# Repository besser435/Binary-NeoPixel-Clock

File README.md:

# Lightbeam S3
 
TODO:<br>
Take picutres<br>
Make CP build and upload to CP website<br>

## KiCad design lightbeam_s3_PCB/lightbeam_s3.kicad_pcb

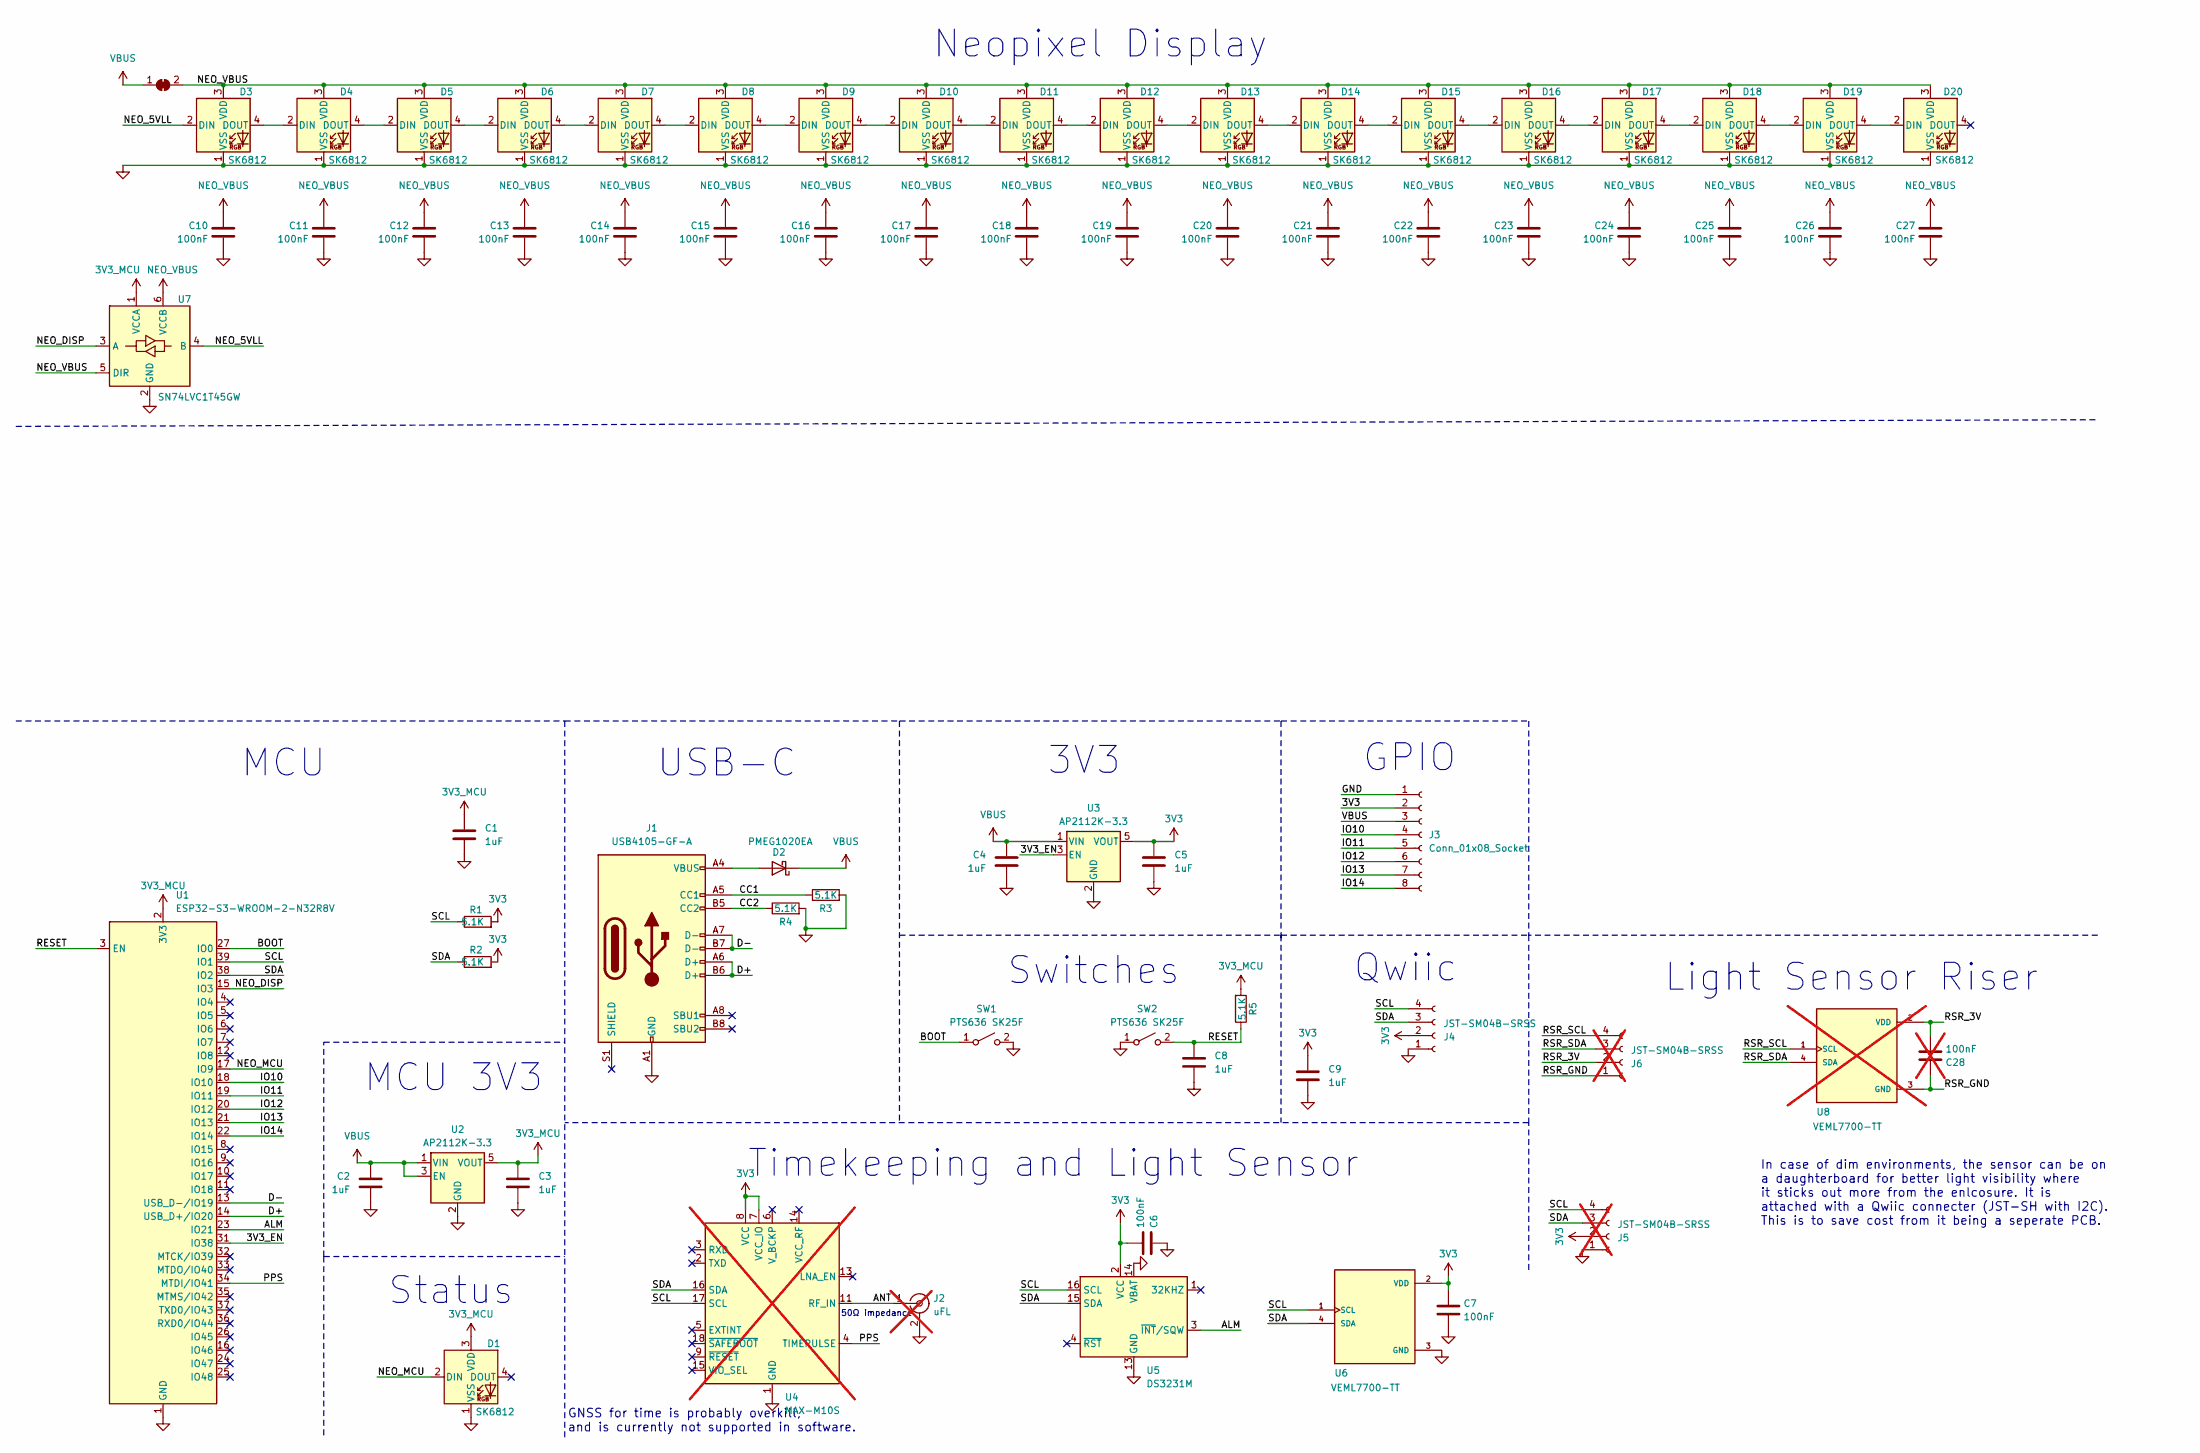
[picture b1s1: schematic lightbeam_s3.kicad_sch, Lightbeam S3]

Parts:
C1, C2, C3, C4, C5, C8, C9: 1uF; C_0603_1608Metric
C6, C7, C10, C11, C12, C13, C14, C15, C16, C17, C18, C19, C20, C21, C22, C23, C24, C25, C26, C27: 100nF; C_0603_1608Metric
C28: 100nF; C_0603_1608Metric; not fitted
D1, D3, D4, D5, D6, D7, D8, D9, D10, D11, D12, D13, D14, D15, D16, D17, D18, D19, D20: SK6812; LED_SK6812_PLCC4_5.0x5.0mm_P3.2mm
D2: PMEG1020EA; D_SOD-323
J1: USB4105-GF-A; USB_C_Receptacle_GCT_USB4105-xx-A_16P_TopMnt_Horizontal
J2: uFL; U.FL_Hirose_U.FL-R-SMT-1_Vertical; not fitted
J3: Conn_01x08_Socket; PinHeader_1x08_P2.54mm_Vertical
J4: JST-SM04B-SRSS; JST_SH_SM04B-SRSS-TB_1x04-1MP_P1.00mm_Horizontal
J5, J6: JST-SM04B-SRSS; JST_SH_SM04B-SRSS-TB_1x04-1MP_P1.00mm_Horizontal; not fitted
JP3: SolderJumper_2_Bridged; solder_jumper_bridged
R1, R2, R3, R4, R5: 5.1K; C_0603_1608Metric
SW1, SW2: PTS636 SK25F; SW_Tactile_SPST_NO_Straight_CK_PTS636Sx25SMTRLFS
U1: ESP32-S3-WROOM-2-N32R8V; ESP32-S3-WROOM-2
U2, U3: AP2112K-3.3; SOT-23-5
U4: MAX-M10S; ublox_MAX; not fitted
U5: DS3231M; SOIC-16W_7.5x10.3mm_P1.27mm
U6: VEML7700-TT; VEML7700; PARTREV 1.6
U7: SN74LVC1T45GW; SOT-363_SC-70-6
U8: VEML7700-TT; VEML7700; PARTREV 1.6; not fitted

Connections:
3V3: C5.1, C6.1, C7.2, C9.1, J3.2, J4.2, J5.2, R1.2, R2.2, U3.5 (VOUT), U4.7 (VCC_IO), U4.8 (VCC), U5.2 (VCC), U6.2 (VDD)
3V3_MCU: C1.1, C3.1, D1.3 (VDD), R5.2, U1.2 (3V3), U2.5 (VOUT), U7.1 (VCCA)
/3V3_EN: U1.31 (IO38), U3.3 (EN)
/ALM: U1.23 (IO21), U5.3 (~INT/SQW)
/ANT: J2.1 (In), U4.11 (RF_IN)
/BOOT: SW1.1 (A), U1.27 (IO0)
/CC1: J1.A5 (CC1), R3.1
/CC2: J1.B5 (CC2), R4.1
/D+: J1.A6 (D+), J1.B6 (D+), U1.14 (USB_D+/IO20)
/D-: J1.A7 (D-), J1.B7 (D-), U1.13 (USB_D-/IO19)
/IO10: J3.4, U1.18 (IO10)
/IO11: J3.5, U1.19 (IO11)
/IO12: J3.6, U1.20 (IO12)
/IO13: J3.7, U1.21 (IO13)
/IO14: J3.8, U1.22 (IO14)
/NEO_5VLL: D3.2 (DIN), U7.4 (B)
/NEO_DISP: U1.15 (IO3), U7.3 (A)
/NEO_MCU: D1.2 (DIN), U1.17 (IO9)
/PPS: U1.34 (MTDI/IO41), U4.4 (TIMEPULSE)
/RESET: C8.1, R5.1, SW2.2 (B), U1.3 (EN)
/RSR_3V: C28.1, J6.2, U8.2 (VDD)
/RSR_GND: C28.2, J6.1, U8.3 (GND)
/RSR_SCL: J6.4, U8.1 (SCL)
/RSR_SDA: J6.3, U8.4 (SDA)
/SCL: J4.4, J5.4, R1.1, U1.39 (IO1), U4.17 (SCL), U5.16 (SCL), U6.1 (SCL)
/SDA: J4.3, J5.3, R2.1, U1.38 (IO2), U4.16 (SDA), U5.15 (SDA), U6.4 (SDA)
GND: C1.2, C2.1, C3.2, C4.1, C5.2, C6.2, C7.1, C8.2, C9.2, C10.1, C11.1, C12.1, C13.1, C14.1, C15.1, C16.1, C17.1, C18.1, C19.1, C20.1, C21.1, C22.1, C23.1, C24.1, C25.1, C26.1, C27.1, D1.1 (VSS), D3.1 (VSS), D4.1 (VSS), D5.1 (VSS), D6.1 (VSS), D7.1 (VSS), D8.1 (VSS), D9.1 (VSS), D10.1 (VSS), D11.1 (VSS), D12.1 (VSS), D13.1 (VSS), D14.1 (VSS), D15.1 (VSS), D16.1 (VSS), D17.1 (VSS), D18.1 (VSS), D19.1 (VSS), D20.1 (VSS), J1.A1 (GND), J1.A12 (GND), J1.B1 (GND), J1.B12 (GND), J2.2 (Ext), J3.1, J4.1, J5.1, R3.2, R4.2, SW1.2 (B), SW2.1 (A), U1.1 (GND), U1.40 (GND), U1.41 (GND), U2.2 (GND), U3.2 (GND), U4.1 (GND), U4.10 (GND), U4.12 (GND), U5.5 (GND), U5.6 (GND), U5.7 (GND), U5.8 (GND), U5.9 (GND), U5.10 (GND), U5.11 (GND), U5.12 (GND), U5.13 (GND), U5.14 (VBAT), U6.3 (GND), U7.2 (GND)
NEO_VBUS: C10.2, C11.2, C12.2, C13.2, C14.2, C15.2, C16.2, C17.2, C18.2, C19.2, C20.2, C21.2, C22.2, C23.2, C24.2, C25.2, C26.2, C27.2, D3.3 (VDD), D4.3 (VDD), D5.3 (VDD), D6.3 (VDD), D7.3 (VDD), D8.3 (VDD), D9.3 (VDD), D10.3 (VDD), D11.3 (VDD), D12.3 (VDD), D13.3 (VDD), D14.3 (VDD), D15.3 (VDD), D16.3 (VDD), D17.3 (VDD), D18.3 (VDD), D19.3 (VDD), D20.3 (VDD), JP3.2 (B), U7.5 (DIR), U7.6 (VCCB)
unnamed: D2.2 (A), J1.A4 (VBUS), J1.A9 (VBUS), J1.B4 (VBUS), J1.B9 (VBUS)
unnamed: D3.4 (DOUT), D4.2 (DIN)
unnamed: D4.4 (DOUT), D5.2 (DIN)
unnamed: D5.4 (DOUT), D6.2 (DIN)
unnamed: D6.4 (DOUT), D7.2 (DIN)
unnamed: D7.4 (DOUT), D8.2 (DIN)
unnamed: D8.4 (DOUT), D9.2 (DIN)
unnamed: D9.4 (DOUT), D10.2 (DIN)
unnamed: D10.4 (DOUT), D11.2 (DIN)
unnamed: D11.4 (DOUT), D12.2 (DIN)
unnamed: D12.4 (DOUT), D13.2 (DIN)
unnamed: D13.4 (DOUT), D14.2 (DIN)
unnamed: D14.4 (DOUT), D15.2 (DIN)
unnamed: D15.4 (DOUT), D16.2 (DIN)
unnamed: D16.4 (DOUT), D17.2 (DIN)
unnamed: D17.4 (DOUT), D18.2 (DIN)
unnamed: D18.4 (DOUT), D19.2 (DIN)
unnamed: D19.4 (DOUT), D20.2 (DIN)
VBUS: C2.2, C4.2, D2.1 (K), J3.3, JP3.1 (A), U2.1 (VIN), U2.3 (EN), U3.1 (VIN)

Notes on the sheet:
Neopixel Display
MCU 3V3
50Ω impedance
In case of dim environments, the sensor can be on a daughterboard for better light visibility where it sticks out more from the enlcosure. It is attached with a Qwiic connecter (JST-SH with I2C). This is to save cost from it being a seperate PCB.
GPIO
USB-C
3V3
GNSS for time is probably overkill, and is currently not supported in software.
Timekeeping and Light Sensor
MCU
Status
Qwiic
Light Sensor Riser
Switches

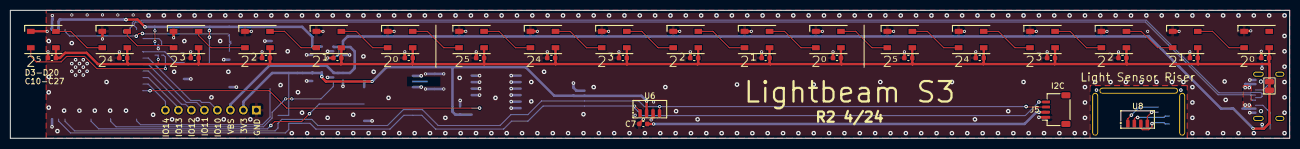
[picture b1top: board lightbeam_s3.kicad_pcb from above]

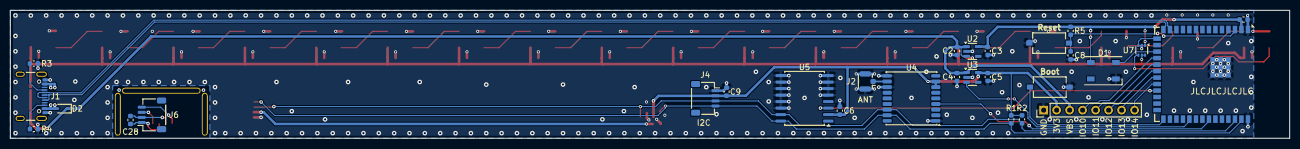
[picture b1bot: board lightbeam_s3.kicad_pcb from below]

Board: 4 copper layers, 250.0 x 25.0 mm, 70 parts (29 on the bottom side), 47 nets.

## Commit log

2023-10-30 Update stuff
2023-10-31 Update binary_clock
2023-12-11 Fix sync bug
2024-03-21 Update gitignore, PCB
2024-03-21 Update PCB
2024-03-21 Start on PCB
2024-03-26 Add final footprint positions
2024-03-26 Change schematic, start routing
2024-03-29 Almost finish placements
2024-03-29 fghxfhxcfhxfhgxfgh sxrfhxfr v
2024-03-30 dead :pensive:
2024-03-31 Add gerber files
2024-03-31 Fix silkscreen part designators
2024-04-03 tthhhhhhhhhhhhhhhhhhhhhhhhhhhhhhhhhhhhhhhhhhhhhhhhhh
2024-04-10 Fix minor bugs, improve holes
2024-04-10 Rename to "Lightbeam S3"
2024-04-10 Move files
2024-04-11 Increase diode to 2A
2024-04-12 Fix I2C lines, remove edge power line
2024-04-12 Improve grounding, move USB lines inward
2024-04-13 Add new Lightbeam, clock software
2024-04-14 DNP GNSS module
2024-04-17 Add 3MF files for Bambu Lab P1S
2024-04-17 Improve PCB for the enclosure, clean traces, DNP GNSS
2024-05-27 Slight PCB changes
2024-05-27 Add safemode.py hack, other minor changes
2024-06-21 Fix debug print times, remove old function, start with display off
